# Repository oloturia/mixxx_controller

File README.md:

A simple project that transform an Arduino Leonardo (or similar boards based on ATmega32u4) in a mixing console for open source Mixxx DJ software. To compile, you'll need MIDIUSB and EncoderButton libraries. Both are downloadable from the official Arduino IDE's library manager.

After uploading the sketch and connecting the controls, you'll have to "train" Mixxx to recognize the various sliders and knobs: click "Learning Wizard" and then follow the instructions. Some of the commands aren't selectable from the interface, you'll need to use the drop down menu to select them (i.e. "scroll up/down the library"). An example configuration is in the folder of the same name. You have to copy the .xml into /home/<user>/.mixxx/controllers/ folder.

Be aware that the controller needs to be plugged in before starting Mixxx. If you enabled the debug, you have to open a serial console to start the device.

At the moment it supports these kinds of controls:
- Analog controls (knobs, sliders) need to be connected to an analog input.
- Rotary encoders, clk should be connected to an interrupt pin, dt to a digital input.
- Buttons (also on top of rotary encoders) need to be connected to digital input.

Buttons feature single and long press. They could have also two states that toggle (i.e. start/stop, etc.).
Analog controls have three "magnetic" positions: around 0, 1023 and middle (user defined) the reading has more stickyness (user definable). If you see that Mixxx's control is not in the middle when the potentiometer is at its half, alter the middle "magnetic" position.
They have also a dead zone that filters small variations in the readings. If you see that the controls are oscillating, increase the dead zone.

There are two experimental improvements:
- In the "console" folder there is a PCB made in Kicad, ready to be printed. Some of the footprints come from Digi-Key/digikey-kicad-library. The example configuration is trained on this PCB.
- If you need more analog controls, there is a version that features a multiplexer. I've tested with three potentiometers and worked, I've not tested it yet for a full console anyway.

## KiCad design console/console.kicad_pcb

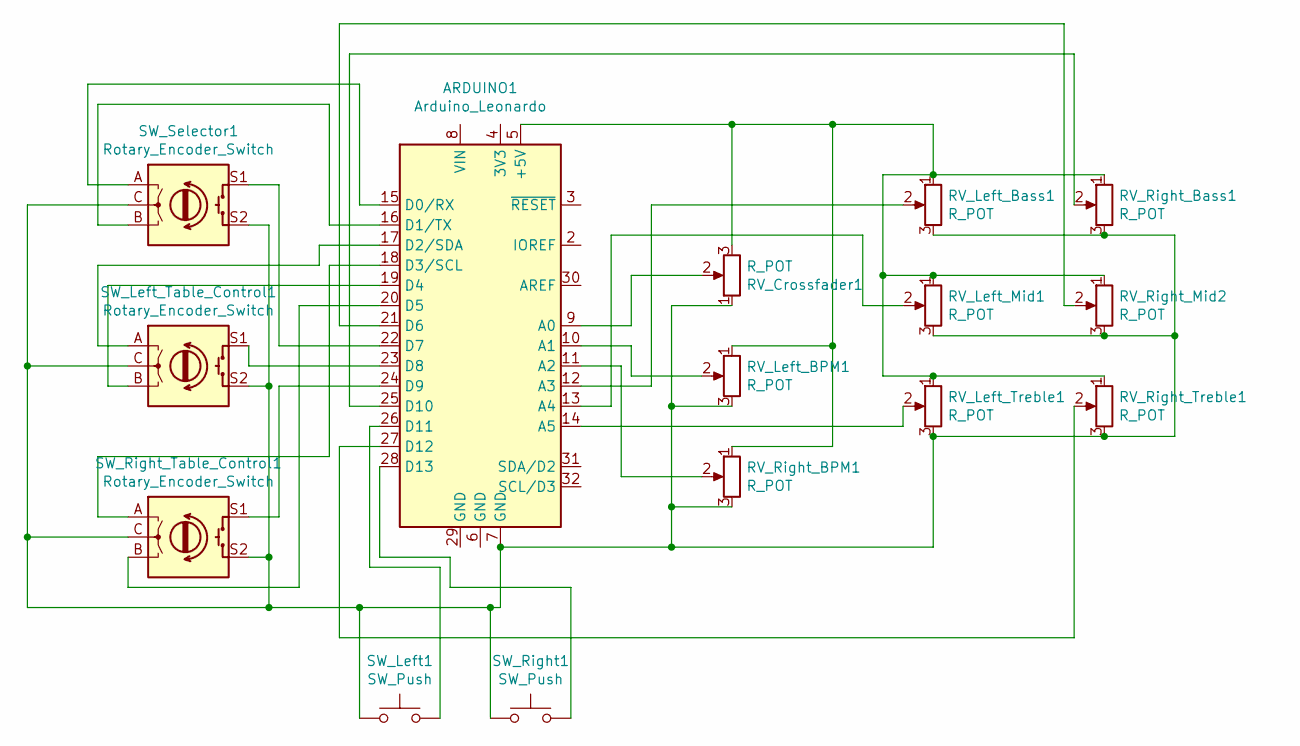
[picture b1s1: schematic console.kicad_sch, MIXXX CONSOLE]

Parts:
ARDUINO1: Arduino_Leonardo; Arduino_UNO_R3
RV_Crossfader1: R_POT; Potentiometer_Bourns_PTA6043_Single_Slide
RV_Left_BPM1: R_POT; Potentiometer_Bourns_PTA4543_Single_Slide
RV_Left_Bass1: R_POT; Potentiometer_Bourns_PTV09A-1_Single_Vertical
RV_Left_Mid1: R_POT; Potentiometer_Bourns_PTV09A-1_Single_Vertical
RV_Left_Treble1: R_POT; Potentiometer_Bourns_PTV09A-1_Single_Vertical
RV_Right_BPM1: R_POT; Potentiometer_Bourns_PTA4543_Single_Slide
RV_Right_Bass1: R_POT; Potentiometer_Bourns_PTV09A-1_Single_Vertical
RV_Right_Mid2: R_POT; Potentiometer_Bourns_PTV09A-1_Single_Vertical
RV_Right_Treble1: R_POT; Potentiometer_Bourns_PTV09A-1_Single_Vertical
SW_Left1: SW_Push; D6R90F2LFS
SW_Left_Table_Control1: Rotary_Encoder_Switch; XDCR_PEC11R-4215F-S0024
SW_Right1: SW_Push; D6R90F2LFS
SW_Right_Table_Control1: Rotary_Encoder_Switch; XDCR_PEC11R-4215F-S0024
SW_Selector1: Rotary_Encoder_Switch; XDCR_PEC11R-4215F-S0024

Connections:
unnamed: ARDUINO1.5 (+5V), RV_Crossfader1.3, RV_Left_BPM1.1, RV_Left_Bass1.1, RV_Left_Mid1.1, RV_Left_Treble1.1, RV_Right_BPM1.1, RV_Right_Bass1.1, RV_Right_Mid2.1, RV_Right_Treble1.1
unnamed: ARDUINO1.7 (GND), RV_Crossfader1.1, RV_Left_BPM1.3, RV_Left_Bass1.3, RV_Left_Mid1.3, RV_Left_Treble1.3, RV_Right_BPM1.3, RV_Right_Bass1.3, RV_Right_Mid2.3, RV_Right_Treble1.3, SW_Left1.1, SW_Left_Table_Control1.C, SW_Left_Table_Control1.S2, SW_Right1.1, SW_Right_Table_Control1.C, SW_Right_Table_Control1.S2, SW_Selector1.C, SW_Selector1.S2
unnamed: ARDUINO1.9 (A0), RV_Crossfader1.2
unnamed: ARDUINO1.10 (A1), RV_Left_BPM1.2
unnamed: ARDUINO1.11 (A2), RV_Right_BPM1.2
unnamed: ARDUINO1.12 (A3), RV_Left_Bass1.2
unnamed: ARDUINO1.13 (A4), RV_Left_Mid1.2
unnamed: ARDUINO1.14 (A5), RV_Left_Treble1.2
unnamed: ARDUINO1.15 (D0/RX), SW_Selector1.A
unnamed: ARDUINO1.16 (D1/TX), SW_Selector1.B
unnamed: ARDUINO1.17 (D2/SDA), SW_Left_Table_Control1.A
unnamed: ARDUINO1.18 (D3/SCL), SW_Right_Table_Control1.A
unnamed: ARDUINO1.19 (D4), SW_Left_Table_Control1.B
unnamed: ARDUINO1.20 (D5), SW_Right_Table_Control1.B
unnamed: ARDUINO1.21 (D6), RV_Right_Mid2.2
unnamed: ARDUINO1.22 (D7), SW_Selector1.S1
unnamed: ARDUINO1.23 (D8), SW_Left_Table_Control1.S1
unnamed: ARDUINO1.24 (D9), SW_Right_Table_Control1.S1
unnamed: ARDUINO1.25 (D10), RV_Right_Bass1.2
unnamed: ARDUINO1.26 (D11), SW_Left1.2
unnamed: ARDUINO1.27 (D12), RV_Right_Treble1.2
unnamed: ARDUINO1.28 (D13), SW_Right1.2

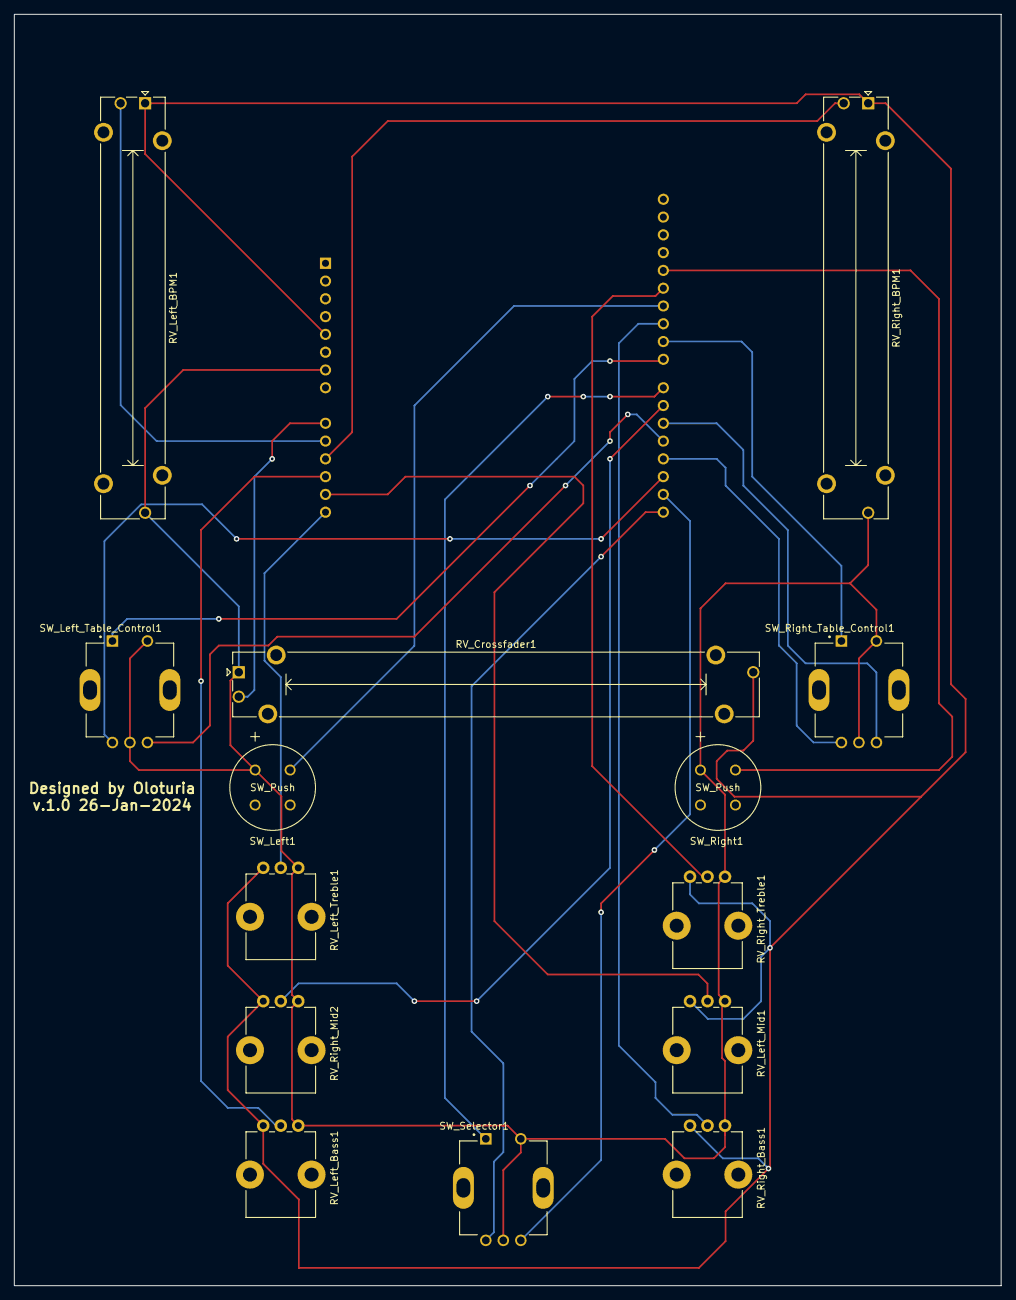
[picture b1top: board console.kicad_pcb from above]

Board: 2 copper layers, 141.0 x 181.6 mm, 15 parts (1 on the bottom side), 22 nets.

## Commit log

2023-05-31 it compiles!
2023-05-31 working
2023-07-11 First working status
2023-07-11 Add LICENSE
2023-07-11 added README
2023-07-28 working encoders
2023-08-01 added digital controls
2023-08-03 added 3rd rotary encoder
2023-08-04 compacted encoders
2023-08-04 double click added
2023-08-04 added toggle functionality
2023-12-04 long click
2023-12-27 added comments
2023-12-27 Added new features: - Dead zones for analog controllers, with stickyness on extreme values (0-1023) and middle (custom value, 512ish). - Separated values that need to be customized for every board (i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
2024-01-05 pcb initialized
2024-01-05 reordered folders
2024-01-16 pcb in progress
2024-01-16 last working commit
2024-01-16 added mux declaration
2024-01-17 added multiplexer support, not tested yet
2024-01-17 cleaned messages
2024-01-19 pcb init
2024-01-20 PCB complete, not tested yet
2024-01-26 added edges
2024-01-26 error corrected, gerber files created
2024-01-27 corrected small error
2024-02-05 PCB tested, working
2024-02-07 better debug output (now with MIDI signals)
2024-02-08 minor fix
2024-03-14 objectified structs
2024-03-16 simplified some code
2024-03-27 updated kicad version, added gitignore
2024-03-27 refined gitignore
2024-03-27 Mux as object, not tested yet

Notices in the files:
parts and their libraries:
Copyright 2016 Accelerated Designs. All rights reserved.
